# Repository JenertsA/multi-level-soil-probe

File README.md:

# multi-level-soil-probe
Design files and firmware for multi level soil probe with LoRa connectivity

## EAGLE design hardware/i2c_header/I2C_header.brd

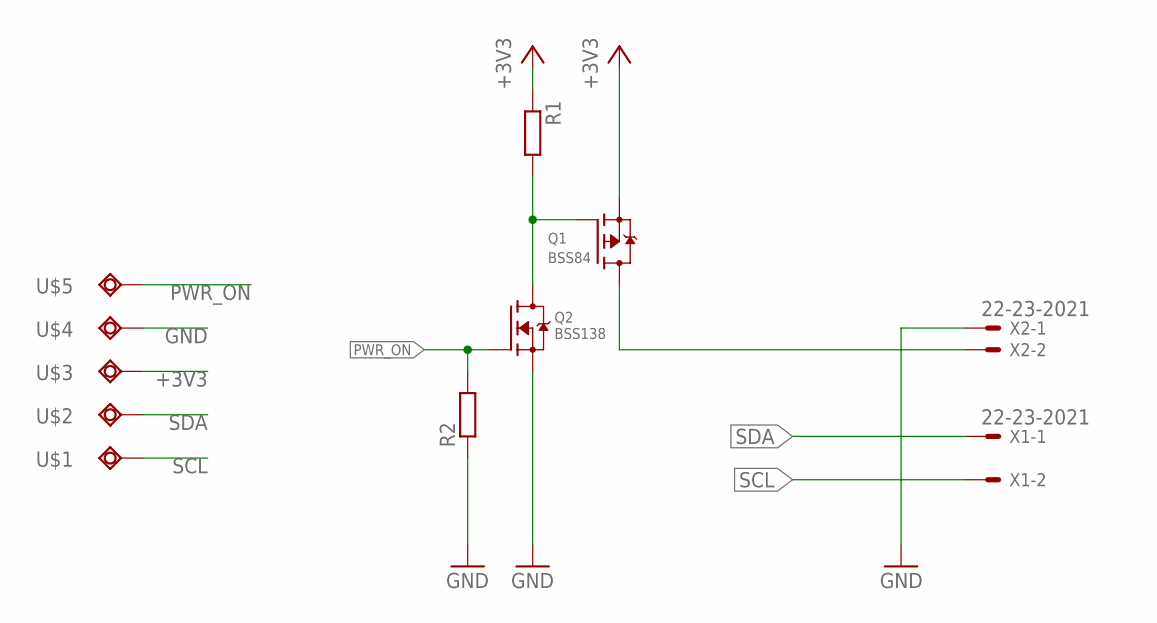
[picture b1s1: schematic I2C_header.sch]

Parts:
Q1: BSS84; SOT-23-3
Q2: BSS138; SOT-23-3
R1, R2: RESISTOR_0805; SMD_0805
U$1, U$2, U$3, U$4, U$5: PAD3.0X5.0; PAD3X5
X1, X2: 22-23-2021

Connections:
+3V3: Q1.2 (S), R1.1, U$3.P$1
GND: Q2.2 (S), R2.1, U$4.P$1, X2.1
unnamed: Q1.3 (D), X2.2
unnamed: Q1.1 (G), Q2.3 (D), R1.2
PWR_ON: Q2.1 (G), R2.2, U$5.P$1
SCL: U$1.P$1, X1.2
SDA: U$2.P$1, X1.1

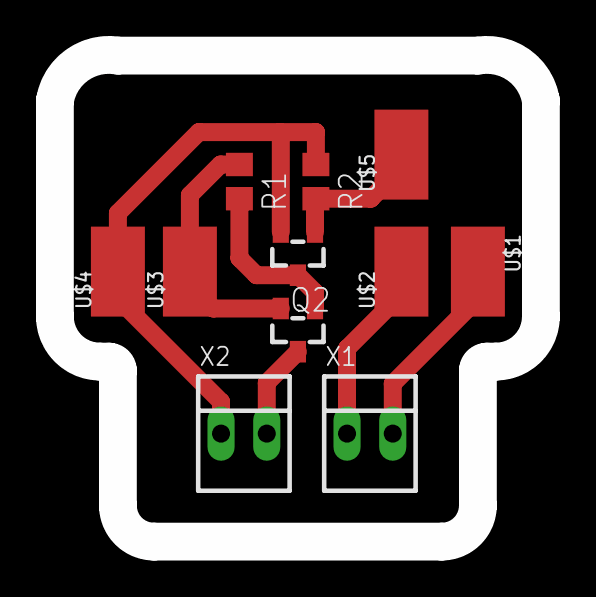
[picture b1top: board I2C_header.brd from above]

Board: 2 copper layers, 27.0 x 27.0 mm, 11 parts (0 on the bottom side), 7 nets.

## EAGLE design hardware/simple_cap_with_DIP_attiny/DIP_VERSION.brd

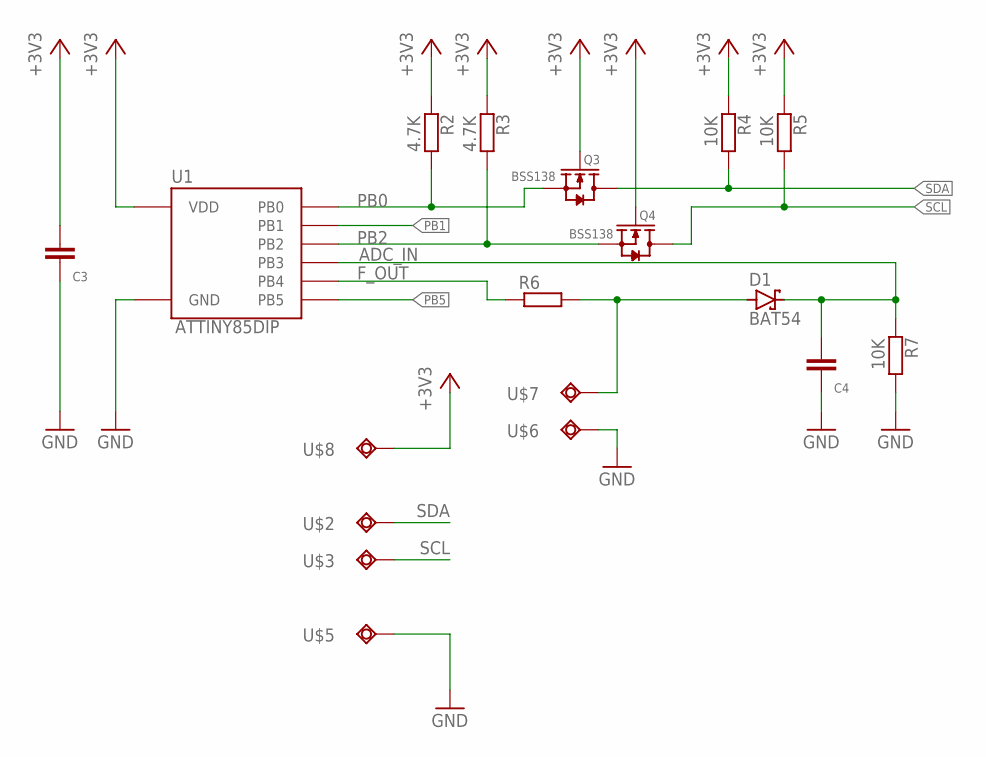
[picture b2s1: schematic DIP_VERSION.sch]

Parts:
C3: 100nF 6.3V; SMD_0805
C4: 10UF 6.3V; SMD_0805
D1: BAT54; SOT23
Q3, Q4: BSS138; SOT-23
R2, R3: 4.7K; SMD_0805
R4, R5, R7: 10K; SMD_0805
R6: 6.25; SMD_0805
U1: ATTINY85DIP; DIP8
U$2, U$3, U$5, U$6, U$7, U$8: PAD3.0X5.0; PAD3X5

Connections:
+3V3: C3.2, Q3.1 (G), Q4.1 (G), R2.1, R3.1, R4.1, R5.1, U1.8 (VDD), U$8.P$1
ADC_IN: C4.2, D1.3 (C), R7.1, U1.2 (PB3)
F_OUT: R6.1, U1.3 (PB4)
GND: C3.1, C4.1, R7.2, U1.4 (GND), U$5.P$1, U$6.P$1
unnamed: D1.1 (A), R6.2, U$7.P$1
PB0: Q3.2 (S), R2.2, U1.5 (PB0)
PB1: U1.6 (PB1)
PB2: Q4.2 (S), R3.2, U1.7 (PB2)
PB5: U1.1 (PB5)
SCL: Q4.3 (D), R5.2, U$3.P$1
SDA: Q3.3 (D), R4.2, U$2.P$1

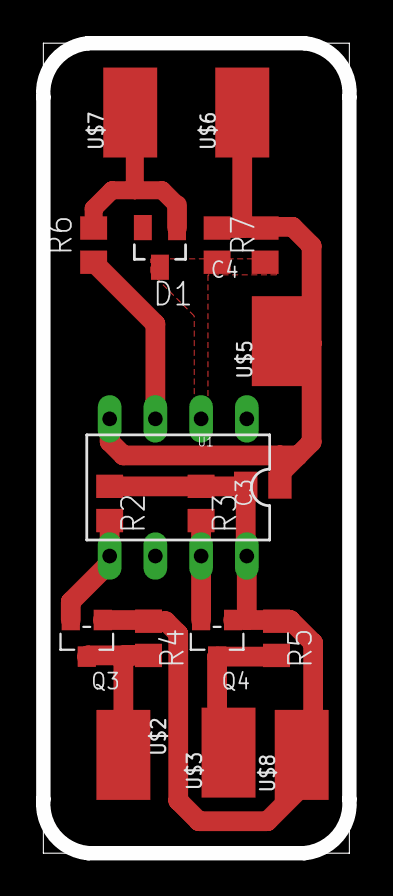
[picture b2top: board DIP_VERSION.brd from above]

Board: 2 copper layers, 17.0 x 45.0 mm, 18 parts (0 on the bottom side), 9 nets.

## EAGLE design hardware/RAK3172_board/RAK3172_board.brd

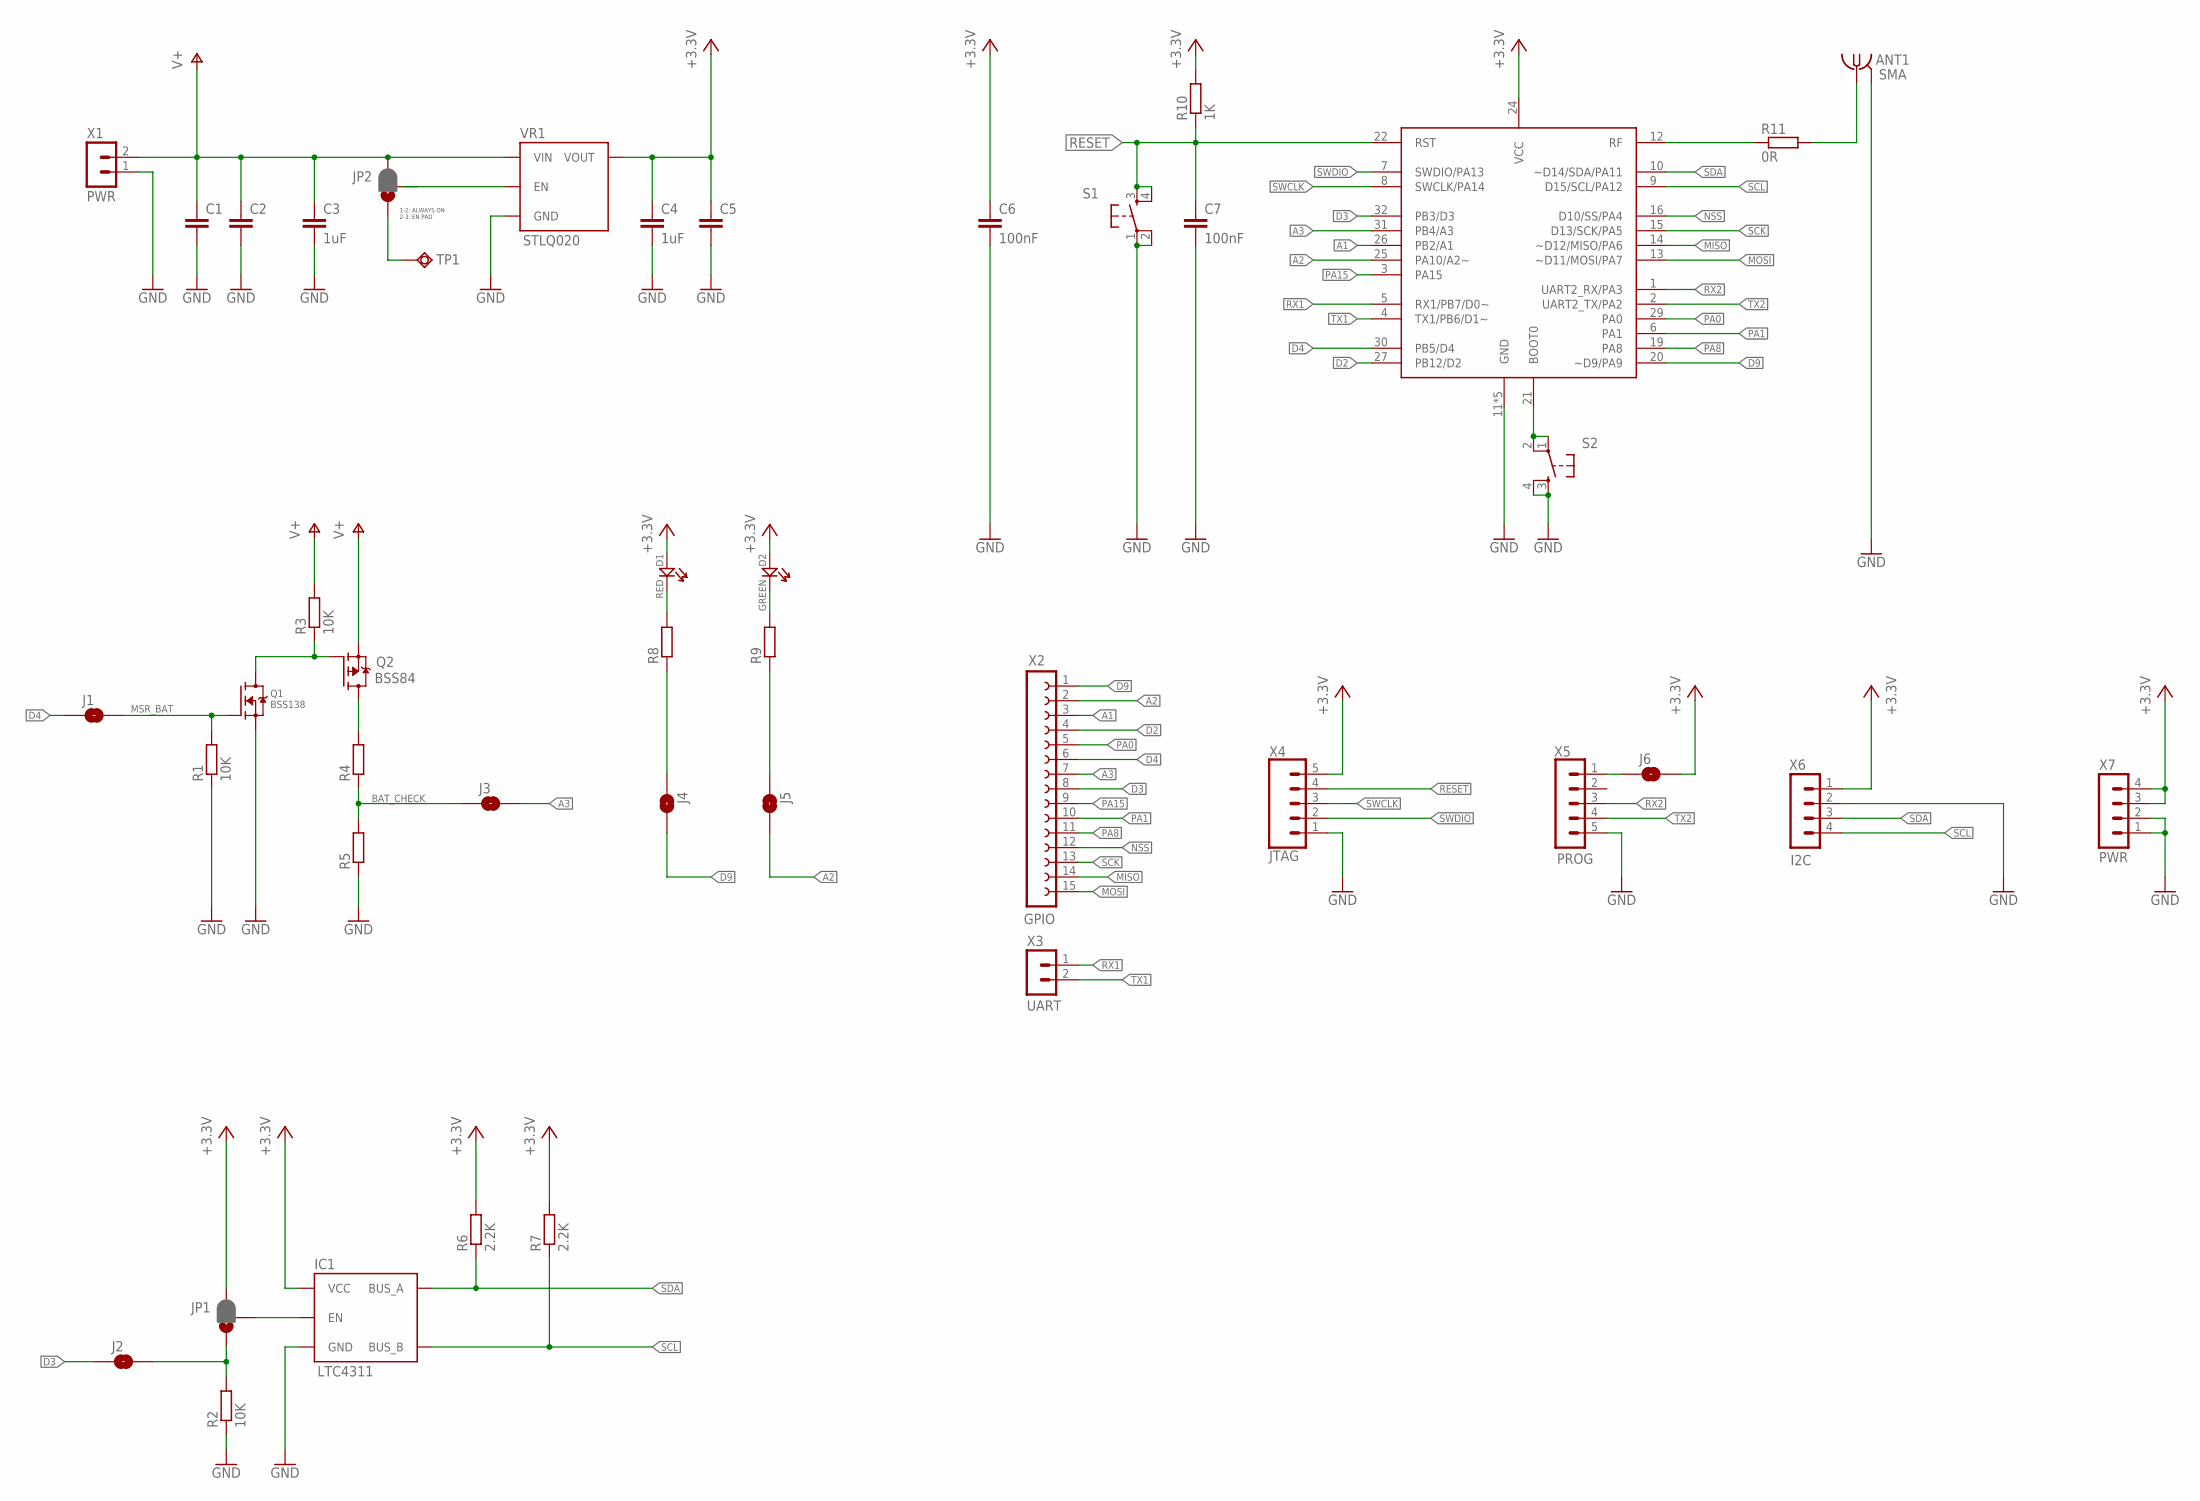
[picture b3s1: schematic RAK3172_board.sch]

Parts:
ANT1: SMA; SMA_1MM
C1, C2, C5: CAP_CERAMIC_0603; SMD_0603C
C3, C4: 1uF; SMD_0603C
C6, C7: 100nF; SMD_0603C
D1: RED; LED-0805
D2: GREEN; LED-0805
IC1: LTC4311; SC-70-6
IC2: RAK3172HF; RAK3172
J1, J2, J3, J4, J5, J6: SMD_JUMP_2_NO_N; SMT_JUMP_2_NO
JP1, JP2: JUMPER-SMT_3_1-NC_PASTE_SILK; SMT-JUMPER_3_1-NC_PASTE_SILK
Q1: BSS138; SOT-23-3
Q2: BSS84; SOT-23-3
R1, R2, R3: 10K; SMD_0603
R4, R5, R8, R9: RESISTOR_0603; SMD_0603
R6, R7: 2.2K; SMD_0603
R10: 1K; SMD_0603
R11: 0R; SMD_0603
S1, S2: BTNRKB2; RKB2
TP1: PAD1.5X3.0
VR1: STLQ020; SOT323-5L
X1: PWR; JST-PH_2
X2: GPIO; 1X15
X3: UART; 1X02
X4: JTAG; 1X05_LOCK
X5: PROG; JST05_2MM
X6: I2C; JST-PH_4
X7: PWR; 2X02

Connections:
+3V3: C4.1, C5.1, C6.1, D1.+, D2.+, IC1.P1 (VCC), IC2.24 (VCC), J6.2, JP1.3, R6.2, R7.2, R10.2, VR1.P$5 (VOUT), X4.5, X6.1, X7.3, X7.4
A1: IC2.26 (PB2/A1), X2.3
A2: IC2.25 (PA10/A2~), J5.2, X2.2
A3: IC2.31 (PB4/A3), J3.2, X2.7
AS: J4.1, R8.1
BAT_CHECK: J3.1, R4.1, R5.2
D2: IC2.27 (PB12/D2), X2.4
D3: IC2.32 (PB3/D3), J2.1, X2.8
D4: IC2.30 (PB5/D4), J1.1, X2.6
D9: IC2.20 (~D9/PA9), J4.2, X2.1
GND/2: ANT1.G@1 (GND), ANT1.G@2 (GND), ANT1.G@3 (GND), ANT1.G@4 (GND), C1.2, C2.2, C3.2, C4.2, C5.2, C6.2, C7.2, IC1.P2 (GND), IC1.P5 (GND), IC2.11 (GND), IC2.17 (GND), IC2.18 (GND), IC2.23 (GND), IC2.28 (GND), Q1.2 (S), R1.1, R2.1, R5.1, S1.1, S1.2 (P1), S2.3 (S), S2.4 (S1), VR1.P$2 (GND), X1.1, X4.1, X5.5, X6.2, X7.1, X7.2
MISO: IC2.14 (~D12/MISO/PA6), X2.14
MOSI: IC2.13 (~D11/MOSI/PA7), X2.15
MSR_BAT: J1.2, Q1.1 (G), R1.2
unnamed: IC2.12 (RF), R11.1
unnamed: IC2.21 (BOOT0), S2.1, S2.2 (P1)
unnamed: ANT1.1, R11.2
unnamed: J6.1, X5.1
unnamed: JP2.2, VR1.P$3 (EN)
unnamed: JP2.1, TP1.P$1
unnamed: Q1.3 (D), Q2.1 (G), R3.1
unnamed: D1.-, R8.2
unnamed: J2.2, JP1.1, R2.2
unnamed: D2.-, R9.2
unnamed: Q2.3 (D), R4.2
unnamed: IC1.P3 (EN), JP1.2
NSS: IC2.16 (D10/SS/PA4), X2.12
PA0: IC2.29 (PA0), X2.5
PA1: IC2.6 (PA1), X2.10
PA8: IC2.19 (PA8), X2.11
PA15: IC2.3 (PA15), X2.9
QGWEG: J5.1, R9.1
RESET: C7.1, IC2.22 (RST), R10.1, S1.3 (S), S1.4 (S1), X4.4
RX1: IC2.5 (RX1/PB7/D0~), X3.1
RX2: IC2.1 (UART2_RX/PA3), X5.3
SCK: IC2.15 (D13/SCK/PA5), X2.13
SCL: IC1.P6 (BUS_B), IC2.9 (D15/SCL/PA12), R7.1, X6.4
SDA: IC1.P4 (BUS_A), IC2.10 (~D14/SDA/PA11), R6.1, X6.3
SWCLK: IC2.8 (SWCLK/PA14), X4.3
SWDIO: IC2.7 (SWDIO/PA13), X4.2
TX1: IC2.4 (TX1/PB6/D1~), X3.2
TX2: IC2.2 (UART2_TX/PA2), X5.4
V+: C1.1, C2.1, C3.1, JP2.3, Q2.2 (S), R3.2, VR1.P$1 (VIN), X1.2

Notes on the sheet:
1-2: ALWAYS ON 2-3: EN PAD

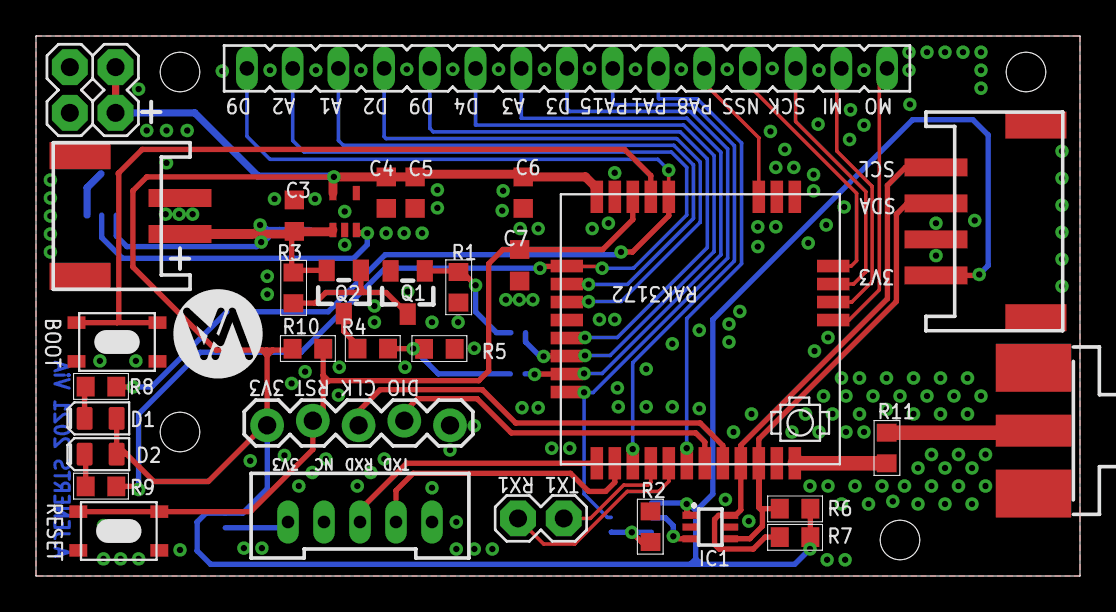
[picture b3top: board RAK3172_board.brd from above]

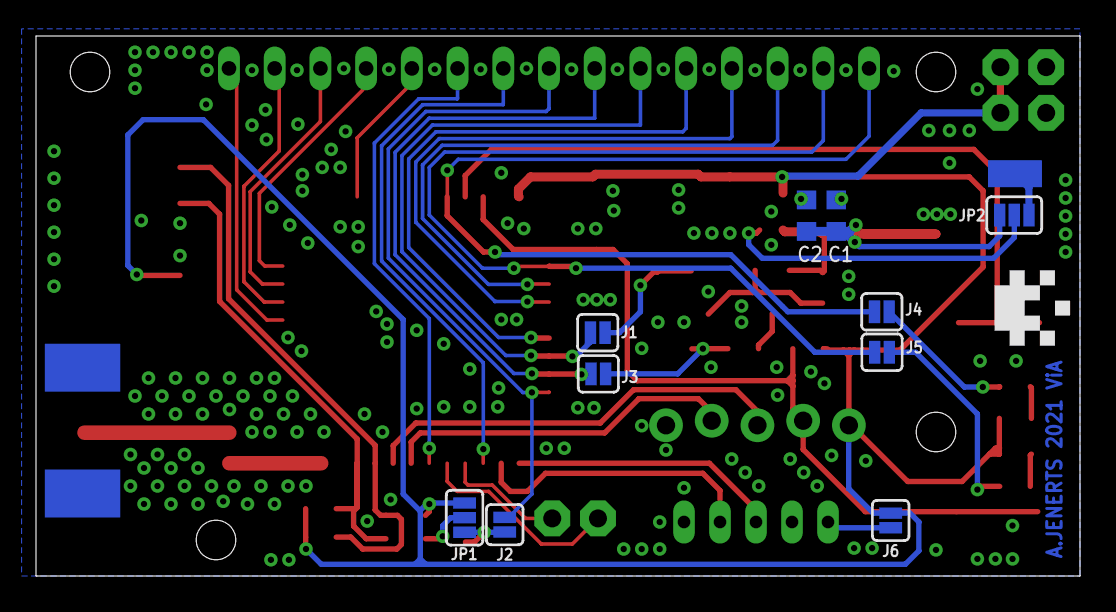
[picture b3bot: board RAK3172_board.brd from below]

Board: 2 copper layers, 58.0 x 30.0 mm, 45 parts (12 on the bottom side), 43 nets.

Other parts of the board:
U$3: A.JENERTS_5MM

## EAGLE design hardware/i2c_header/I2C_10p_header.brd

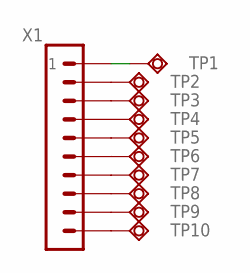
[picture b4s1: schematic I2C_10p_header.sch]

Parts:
TP1, TP2, TP3, TP4, TP5, TP6, TP7, TP8, TP9, TP10: PAD1.5X3.0
X1: FFC_10PV; FFC_1X10_VERTICAL

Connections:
unnamed: TP1.P$1, X1.P$1 (1)
unnamed: TP2.P$1, X1.P$2 (2)
unnamed: TP3.P$1, X1.P$3 (3)
unnamed: TP4.P$1, X1.P$4 (4)
unnamed: TP5.P$1, X1.P$5 (5)
unnamed: TP6.P$1, X1.P$6 (6)
unnamed: TP7.P$1, X1.P$7 (7)
unnamed: TP8.P$1, X1.P$8 (8)
unnamed: TP9.P$1, X1.P$9 (9)
unnamed: TP10.P$1, X1.P$10 (10)

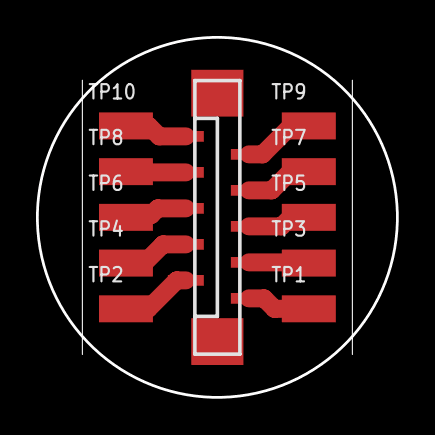
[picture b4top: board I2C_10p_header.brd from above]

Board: 2 copper layers, 20.0 x 20.0 mm, 11 parts (0 on the bottom side), 10 nets.

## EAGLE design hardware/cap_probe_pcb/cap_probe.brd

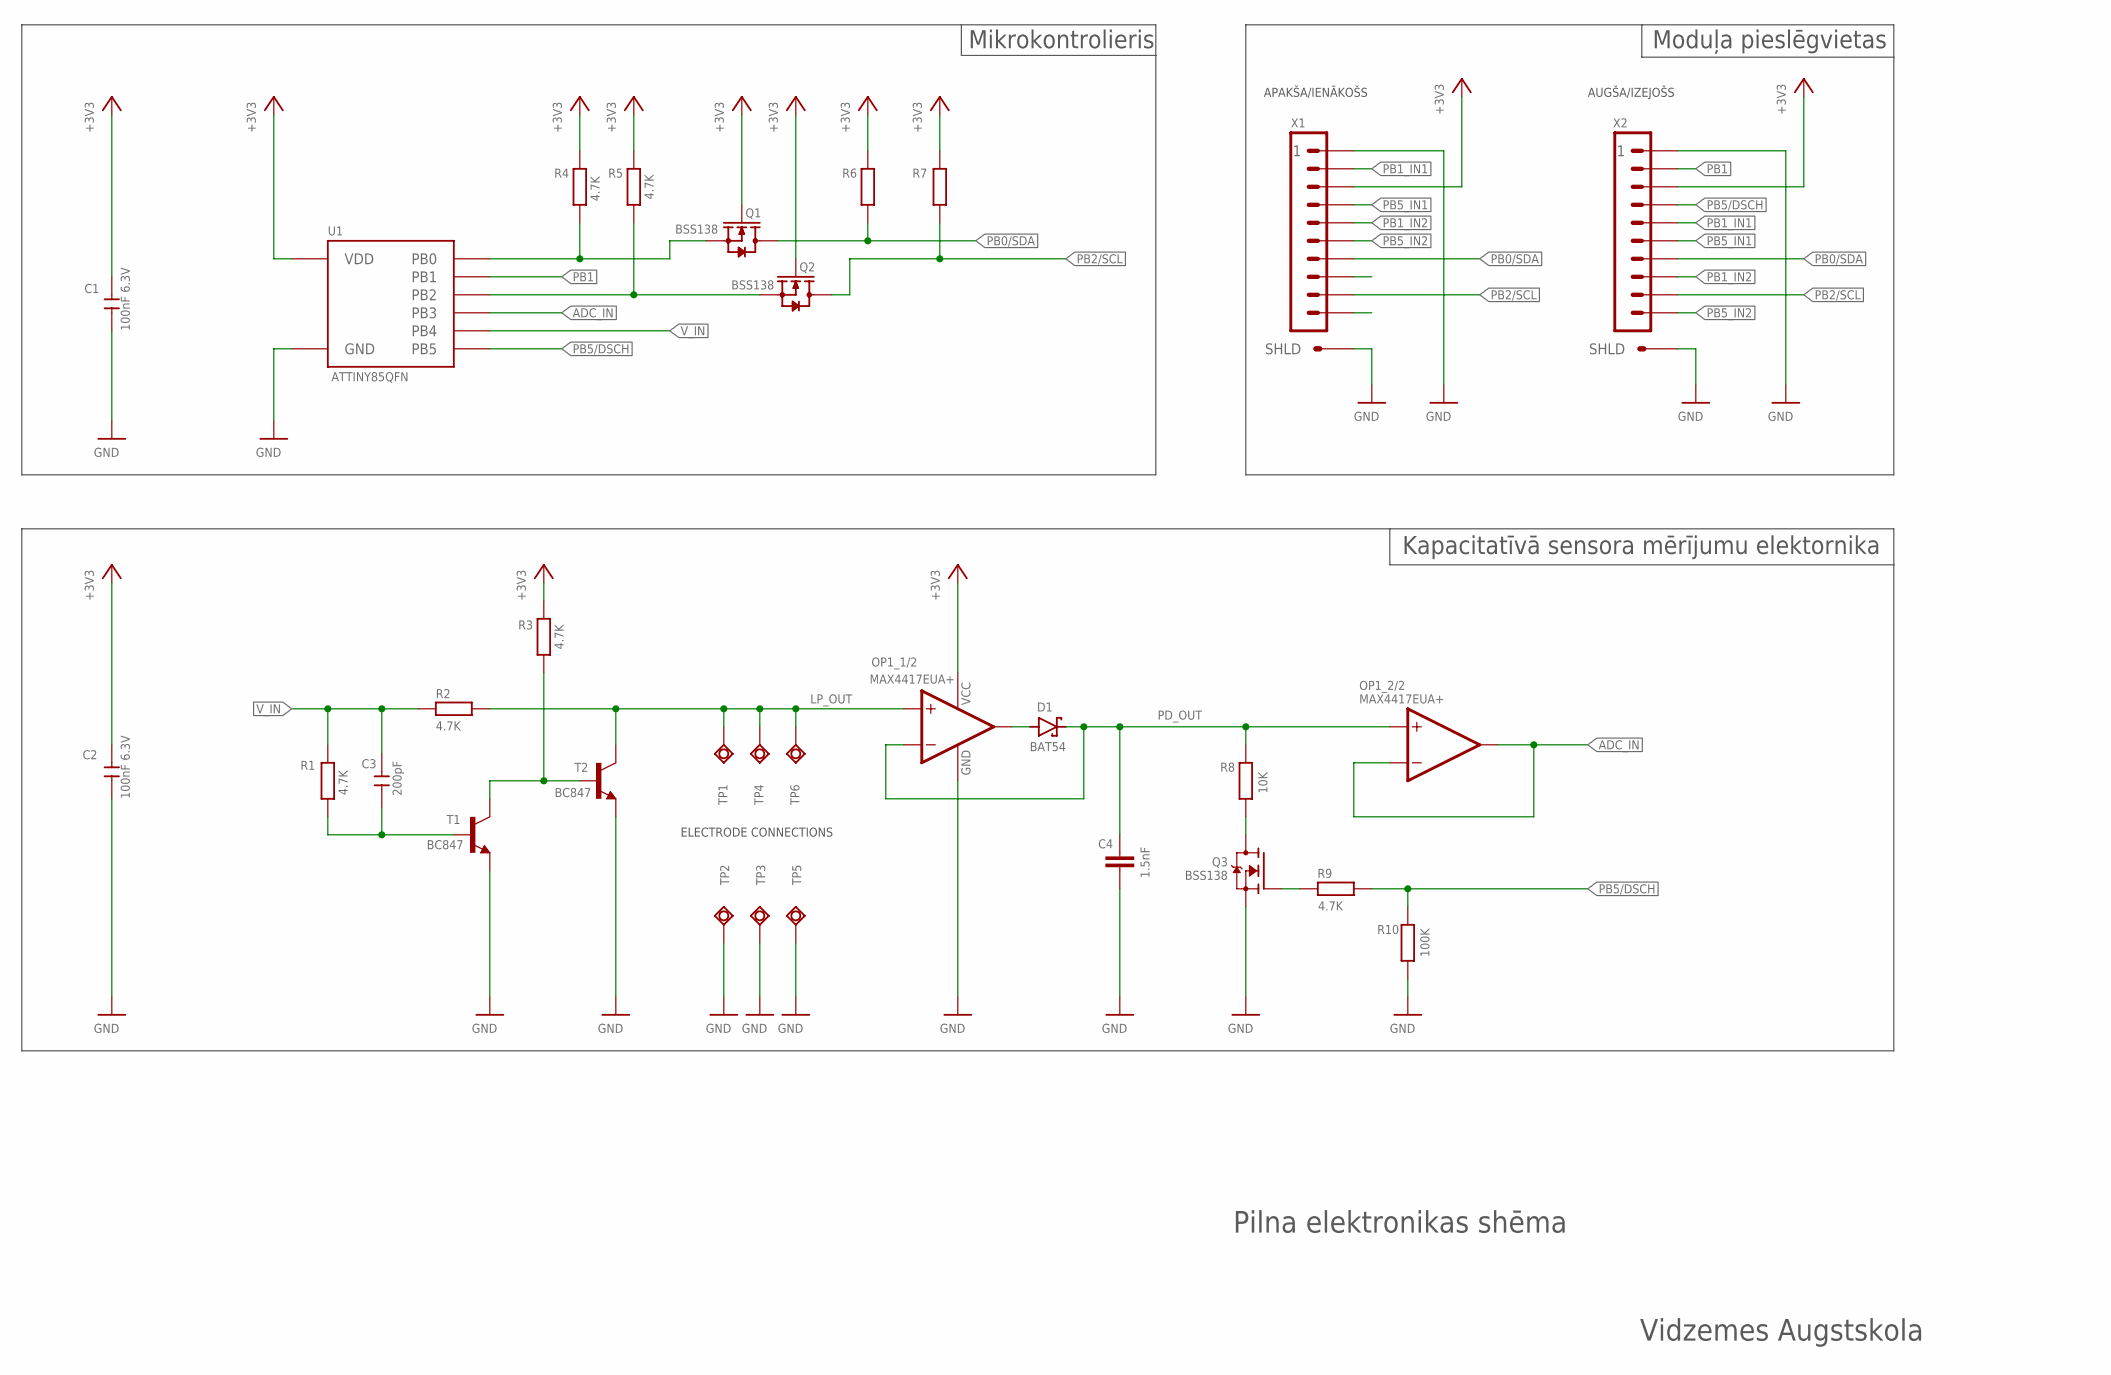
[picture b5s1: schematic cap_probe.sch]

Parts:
C1, C2: 100nF 6.3V; C0402
C3: 200pF; C0402
C4: 1.5nF; SMD_0603C
D1: BAT54; SOT23
OP1: MAX4417EUA+; SOT23-8
Q1, Q2: BSS138; SOT-23
Q3: BSS138; SOT-23-3
R1, R3, R4, R5, R9: 4.7K; R0402
R2: 4.7K; SMD_0603
R6, R7: RESISTOR_0402; R0402
R8: 10K; R0402
R10: 100K; R0402
T1, T2: BC847; SOT23
TP1, TP2, TP3, TP4, TP5, TP6: PAD1.5X3.0
U1: ATTINY85QFN; QFN20_4X4
X1, X2: FFC_10PH; FFC_1.0X10

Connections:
+3V3: C1.2, C2.2, OP1.P$8 (V+), Q1.1 (G), Q2.1 (G), R3.2, R4.2, R5.2, R6.2, R7.2, U1.P$15 (VDD), X1.P$3 (3), X2.P$3 (3)
ADC_IN: OP1.P$6 (-IN), OP1.P$7 (OUT), U1.P$2 (PB3)
GND: C1.1, C2.1, C4.2, OP1.P$4 (V-), Q3.2 (S), R10.2, T1.2 (E), T2.2 (E), TP2.P$1, TP3.P$1, TP5.P$1, U1.P$8 (GND), U1.P$21 (GND), X1.P$1 (1), X1.P$11 (SHLD), X1.P$12 (SHLD), X2.P$1 (1), X2.P$11 (SHLD), X2.P$12 (SHLD)
LP_OUT: OP1.P$3 (+IN), R2.2, T2.3 (C), TP1.P$1, TP4.P$1, TP6.P$1
unnamed: C3.1, R1.1, T1.1 (B)
unnamed: D1.1 (A), OP1.P$1 (OUT)
unnamed: R3.1, T1.3 (C), T2.1 (B)
unnamed: Q3.3 (D), R8.1
unnamed: Q3.1 (G), R9.2
PB0: Q1.2 (S), R4.1, U1.P$11 (PB0)
PB0/SDA: Q1.3 (D), R6.1, X1.P$7 (7), X2.P$7 (7)
PB1: U1.P$12 (PB1), X2.P$2 (2)
PB1_IN1: X1.P$2 (2), X2.P$5 (5)
PB1_IN2: X1.P$5 (5), X2.P$8 (8)
PB2/SCL: Q2.3 (D), R7.1, X1.P$9 (9), X2.P$9 (9)
PB3: Q2.2 (S), R5.1, U1.P$14 (PB2)
PB5/DSCH: R9.1, R10.1, U1.P$1 (PB5), X2.P$4 (4)
PB5_IN1: X1.P$4 (4), X2.P$6 (6)
PB5_IN2: X1.P$6 (6), X2.P$10 (10)
PD_OUT: C4.1, D1.3 (C), OP1.P$2 (-IN), OP1.P$5 (+IN), R8.2
V_IN: C3.2, R1.2, R2.1, U1.P$5 (PB4)

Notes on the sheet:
AUGŠA/IZEJOŠS
APAKŠA/IENĀKOŠS
ELECTRODE CONNECTIONS
Vidzemes Augstskola
Pilna elektronikas shēma
Kapacitatīvā sensora mērījumu elektornika
Moduļa pieslēgvietas
Mikrokontrolieris

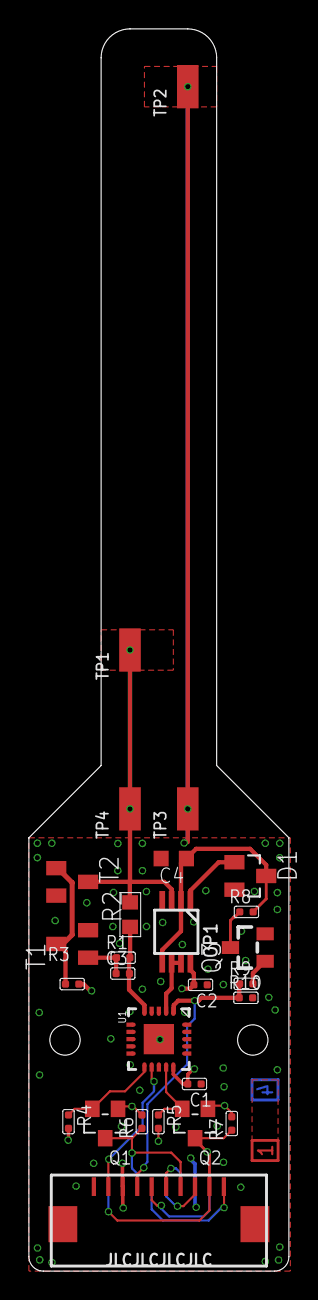
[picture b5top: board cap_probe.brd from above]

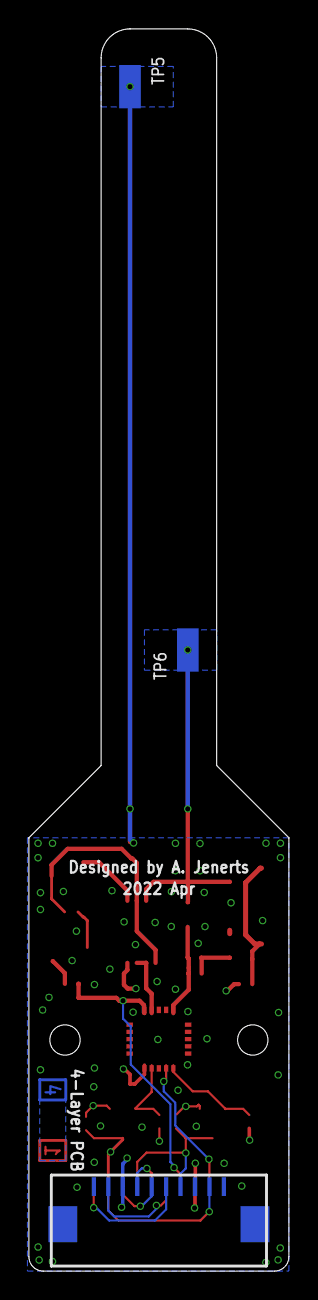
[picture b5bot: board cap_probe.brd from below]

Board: 4 copper layers, 18.0 x 86.0 mm, 30 parts (3 on the bottom side), 21 nets.

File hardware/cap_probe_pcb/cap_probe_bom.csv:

"Qty";"Value";"Device";"Package";"Parts";"Description";"MPN";"POPULARITY";"VALUE";
"2";"";"FFC_10PH";"FFC_1.0X10";"X1, X2";"";"";"";"";
"2";"";"RESISTOR_0402";"R0402";"R6, R7";"";"";"";"";
"1";"1.5nF";"CAP_CERAMIC_0603";"SMD_0603C";"C4";"";"";"";"";
"1";"100K";"RESISTOR_0402";"R0402";"R10";"";"";"";"";
"2";"100nF 6.3V";"CERAMIC-1UF-6.3V-10%-X5R(0402)";"C0402";"C1, C2";"302010003";"CC0402KRX5R5BB105";"";"1UF 6.3V";
"1";"10K";"RESISTOR_0402";"R0402";"R8";"";"";"";"";
"1";"200pF";"CERAMIC-1UF-6.3V-10%-X5R(0402)";"C0402";"C3";"302010003";"CC0402KRX5R5BB105";"";"1UF 6.3V";
"5";"4.7K";"RESISTOR_0402";"R0402";"R1, R3, R4, R5, R9";"";"";"";"";
"1";"4.7K";"RESISTOR_0603";"SMD_0603";"R2";"";"";"";"";
"1";"ATTINY85QFN";"ATTINY85QFN";"QFN20_4X4";"U1";"The high-performance, low-power Microchip 8-bit AVR RISC-based microcontroller combines 8KB ISP flash memory,";"";"";"";
"1";"BAT54";"BAT54";"SOT23";"D1";"Schottky Diodes";"";"2";"";
"2";"BC847";"BC847";"SOT23";"T1, T2";"NPN TRANSISTOR";"";"5";"";
"1";"BSS138";"BSS138";"SOT-23-3";"Q3";"";"";"";"";
"2";"BSS138";"SMD-MOSFET-N-CH-50V-200MA-BSS138W-7-F(SOT-23)";"SOT-23";"Q1, Q2";"305030000";"BSS138W-7-F";"";"BSS138W-7-F";
"1";"MAX4417EUA+";"MAX_OP_AMPUMAX";"SOT23-8";"OP1";"";"";"";"";
"6";"PAD1.5X3.0";"PAD1.5X3.0";"PAD1.5X3.0";"TP1, TP2, TP3, TP4, TP5, TP6";"";"";"";"";

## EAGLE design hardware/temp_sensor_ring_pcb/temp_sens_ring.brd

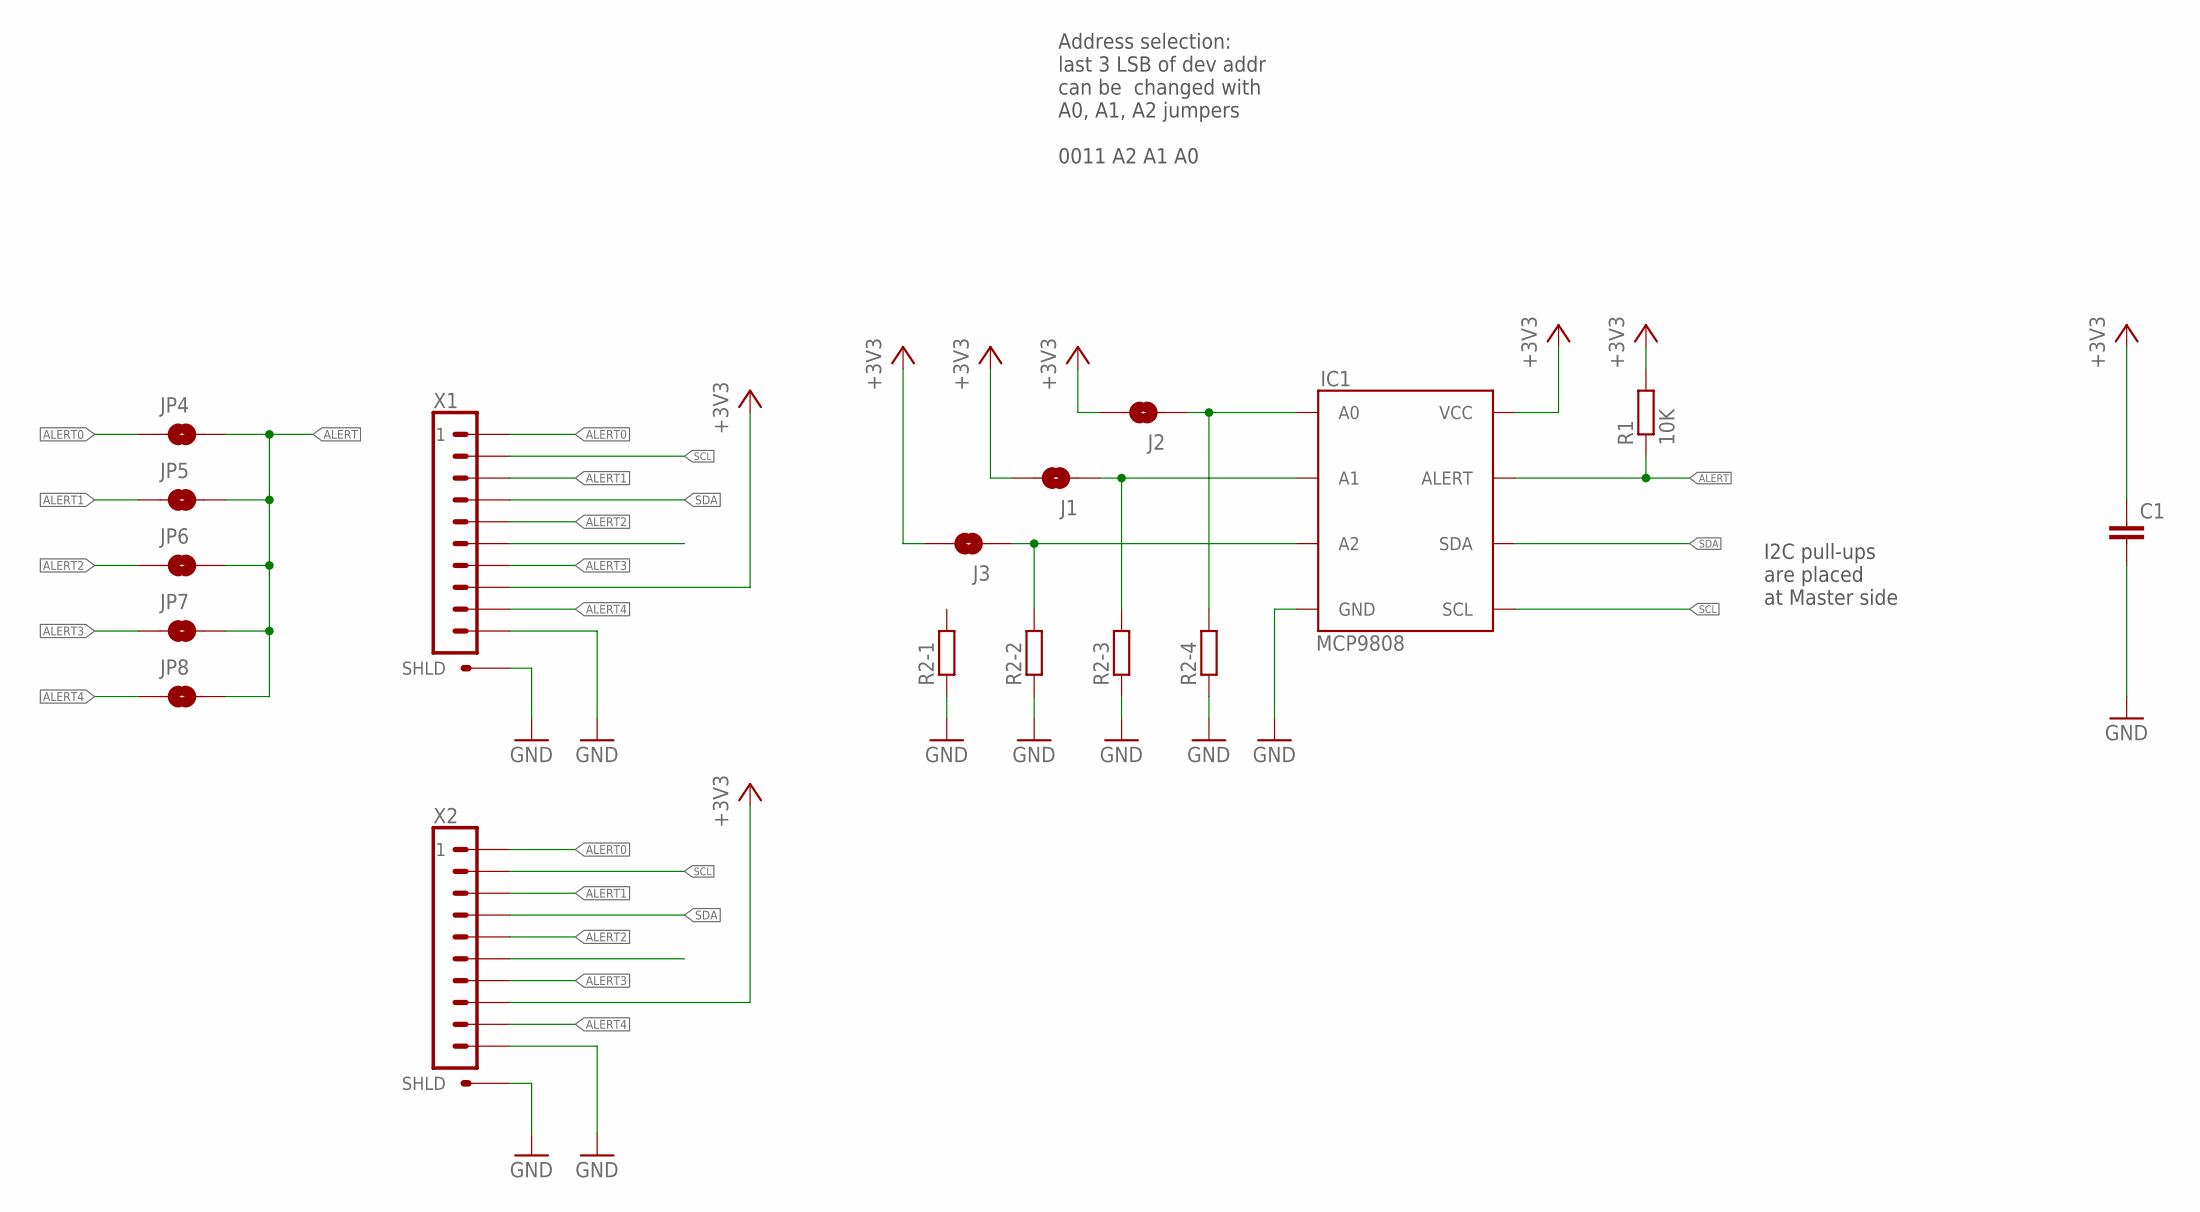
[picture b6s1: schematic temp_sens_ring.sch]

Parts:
C1: CAP_CERAMIC_0402; C0402
IC1: MCP9808; MSOP-8
J1, J2, J3: SMD_JUMP_2_NO_S; SMT_JUMP_2_NO_SMALL
JP4: AL0; SMT-JUMPER_2_NO_NO-SILK
JP5: AL1; SMT-JUMPER_2_NO_NO-SILK
JP6: AL2; SMT-JUMPER_2_NO_NO-SILK
JP7: AL3; SMT-JUMPER_2_NO_NO-SILK
JP8: AL4; SMT-JUMPER_2_NO_NO-SILK
R1: 10K; 0402
R2: RESISTOR_NET_4-0502; R0502_4X
X1, X2: FFC_10PV; FFC_1X10_VERTICAL; MFR_PART F1002-B-10-20T-R

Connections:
+3V3: C1.1, IC1.P$8 (VCC), J1.2, J2.2, J3.2, R1.2, X1.P$8 (8), X2.P$8 (8)
ALERT: IC1.P$3 (ALERT), JP4.2, JP5.2, JP6.2, JP7.2, JP8.2, R1.1
ALERT0: JP4.1, X1.P$1 (1), X2.P$1 (1)
ALERT1: JP5.1, X1.P$3 (3), X2.P$3 (3)
ALERT2: JP6.1, X1.P$5 (5), X2.P$5 (5)
ALERT3: JP7.1, X1.P$7 (7), X2.P$7 (7)
ALERT4: JP8.1, X1.P$9 (9), X2.P$9 (9)
GND: C1.2, IC1.P$4 (GND), R2.P$1 (1), R2.P$2 (1), R2.P$3 (1), R2.P$4 (1), X1.P$10 (10), X1.P$11 (SHLD), X1.P$12 (SHLD), X2.P$10 (10), X2.P$11 (SHLD), X2.P$12 (SHLD)
unnamed: IC1.P$5 (A2), J3.1, R2.P$7 (2)
unnamed: IC1.P$6 (A1), J1.1, R2.P$6 (2)
unnamed: IC1.P$7 (A0), J2.1, R2.P$5 (2)
SCL: IC1.P$2 (SCL), X1.P$2 (2), X2.P$2 (2)
SDA: IC1.P$1 (SDA), X1.P$4 (4), X2.P$4 (4)

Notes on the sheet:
Address selection: last 3 LSB of dev addr can be changed with A0, A1, A2 jumpers 0011 A2 A1 A0
I2C pull-ups are placed at Master side

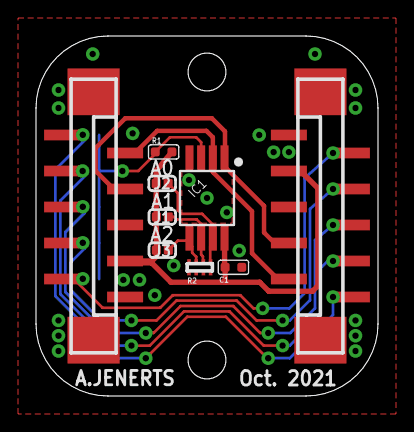
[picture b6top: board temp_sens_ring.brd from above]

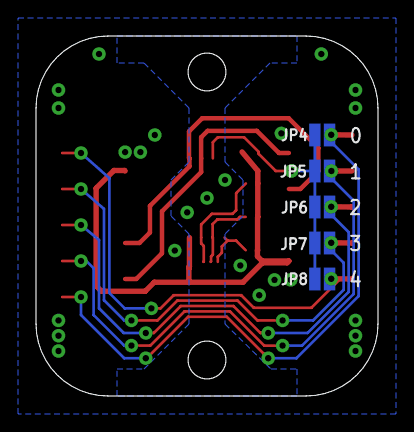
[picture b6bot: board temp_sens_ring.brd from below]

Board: 2 copper layers, 19.0 x 20.0 mm, 14 parts (5 on the bottom side), 13 nets.

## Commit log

2021-10-21 Inital commit of sch
2021-10-23 inital board commit
2021-10-23 Screw holes added
2021-10-27 PCB completed, part library created
2021-10-27 3D models added to library
2021-10-27 3D render added
2021-10-28 Renders updated
2021-10-28 old render removed
2021-10-28 Mounting hole dimension updated for free fit M2
2021-10-28 Single ring assembly drawing added
2021-10-28 folder name changed
2022-01-08 I2C_header board added
2022-01-08 Board dimension added
2022-01-08 PCB production done
2022-01-08 temperature ring sensor CAM files
2022-01-08 vscode config folder added to the gitignore
2022-03-03 OTAA example added
2022-03-03 Temp Example added
2022-03-03 header pinout changed
2022-03-03 updated gitignores
2022-11-21 Combined sensor firmware
2022-11-21 Temp sensor firmware update
2022-11-21 Latest hardware designs
2022-11-21 TTN payload decoder
2022-11-21 Minor edits
2022-11-21 documentation update
2022-11-21 Remove unnecessary readme files

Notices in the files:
parts and their libraries:
SparkFun-Jumpers: Licensing: Creative Commons ShareAlike 4.0 International - https://creativecommons.org/licenses/by-sa/4.0
